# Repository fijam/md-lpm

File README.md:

# md-lpm

This project consists of hardware files and software for a coin-battery operated laser tester that fits in a MiniDisk case.

## Hardware

Schematics, BOM and PCB layout files are available in the hardware directory.

## Theory of operation

This is the nerdy bit, feel free to skip ahead.

The heart of this device is a silicon PIN photodiode (BPW34) operated in reverse-biased mode, which generates current proportional to light intensity. The MiniDisc standard uses 780nm near-infrared laser source for both playback (using the magneto-optic Kerr effect) and recording (for heating up the disc to its Curie temperature). The output power spans between 0.5 and 9mW, depending on the device. 

The selected photodiode has approx. 95% spectral sensitivity at 780nm. The reverse voltage of 3V from a manganese-dioxide lithium battery and load resistance of 1k Ohm allows for a linear response up to 5.5mW as given by: 
`Psat = (0.3 + VR)/RL * S` where VR is the reverse voltage [2.9 V], S is the photosensitivity at 780nm [0.58 A/W] and RL is the load resistance [1000 Ohm]. Photodiode series resistance is disregarded.

High correlation between the photodiode readout (10b referenced to Vdd) and the device refPw setting (in decimal) is achieved:

Shorter fragments of this polynomial (around 0.5-1mW for LrefPw/HrefPw and 4.5-5.5mW for WritPW) can be approximated with a linear regression. 

To discount the effect of battery voltage dropping as it discharges, internal voltage reference of 1.1V is used for LrefPw/HrefPw. For WritPw, the whole range of Vdd is used. The setting of WritPw does not require a high precision.

Each device comes with a calibration factor saved in `user_row` area of the EEPROM which is protected from accidental chip erase. This calibration factor (by default 100%) accounts for differences between components, photodiode alignment and assembly in the minidisc case. It is taken into account when calculating LrefPw and HrefPw.

The firmware of the microcontroller is configured with a BOD of ~2.6V which prevents the device from running on a discharged battery.

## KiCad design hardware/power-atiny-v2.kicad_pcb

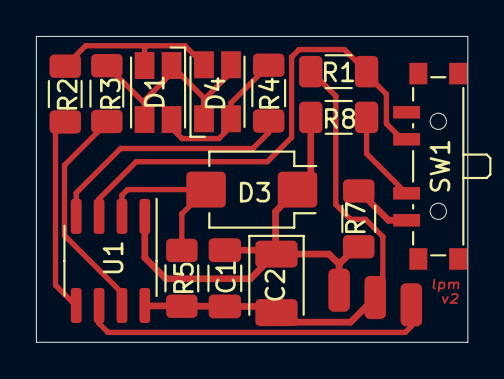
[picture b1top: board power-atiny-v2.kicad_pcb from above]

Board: 2 copper layers, 24.0 x 17.0 mm, 17 parts (0 on the bottom side), 13 nets.

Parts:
C1: 100nF; C_1206_3216Metric_Pad1.33x1.80mm_HandSolder
C2: 68uF; CP_EIA-3528-21_Kemet-B_Pad1.50x2.35mm_HandSolder
D1, D4: LED_Dual_ACAC; LED_Avago_PLCC4_3.2x2.8mm_CW_datasheet
D3: BPW34-SMD; Osram_SMD-DIL2_4.5x4.0mm
GND: SolderWirePad_1x01_SMD_1x2mm
R1: 249k; R_1206_3216Metric_Pad1.30x1.75mm_HandSolder
R2, R3, R4: 220; R_1206_3216Metric_Pad1.30x1.75mm_HandSolder
R5: 1k; R_1206_3216Metric_Pad1.30x1.75mm_HandSolder
R7: 480k; R_1206_3216Metric_Pad1.30x1.75mm_HandSolder
R8: 100k; R_1206_3216Metric_Pad1.30x1.75mm_HandSolder
SW1: SW_SP3T; SW_SP3T_PCM13
U1: ATtiny412-SS; SOIC-8_3.9x4.9mm_P1.27mm
UPDI: SolderWirePad_1x01_SMD_1x2mm
VCC: SolderWirePad_1x01_SMD_1x2mm

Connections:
GND: C1.2, C2.2, GND.1, R1.2, R5.2, U1.8
unnamed: D1.1, D1.4, D4.1, D4.4, R3.1
unnamed: D1.2, D4.3, R2.1
unnamed: D1.3, D4.2, R4.1
unnamed: D3.2, R5.1, U1.2
unnamed: R1.1, SW1.3, U1.3
unnamed: R2.2, U1.5
unnamed: R3.2, U1.7
unnamed: R4.2, U1.4
unnamed: R7.2, SW1.1
unnamed: R8.2, SW1.2
unnamed: U1.6, UPDI.1
VCC: C1.1, C2.1, D3.1, R7.1, R8.1, U1.1, VCC.1

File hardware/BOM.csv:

Id,Designator,Package,Quantity,Designation,Supplier and ref
1,R8,R_1206_3216Metric_Pad1.30x1.75mm_HandSolder,1,100k,
2,R1,R_1206_3216Metric_Pad1.30x1.75mm_HandSolder,1,249k,
3,C2,CP_EIA-3528-21_Kemet-B_Pad1.50x2.35mm_HandSolder,1,68uF,Optional, Kemet T case
4,SW1,SW_SP3T_PCM13,1,SW_SP3T,Nidec Copal CUS-13TB
5,D1,D4,LED_Avago_PLCC4_3.2x2.8mm_CW_datasheet,2,LED_Dual_ACAC,Avago HSMF-C155
6,U1,SOIC-8_3.9x4.9mm_P1.27mm,1,ATtiny412-SS,Microchip ATTINY212-SSNR
7,C1,C_1206_3216Metric_Pad1.33x1.80mm_HandSolder,1,100nF,
8,D3,Osram_SMD-DIL2_4.5x4.0mm,1,BPW34-SMD,Osram BPW34S
9,R2,R3,R4,R_1206_3216Metric_Pad1.30x1.75mm_HandSolder,3,220,
10,R5,R_1206_3216Metric_Pad1.30x1.75mm_HandSolder,1,1k,
11,R7,R_1206_3216Metric_Pad1.30x1.75mm_HandSolder,1,480k,

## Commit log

2022-02-04 Initial import
2022-02-04 Add lpm.py executable (via pyinstaller)
2022-02-04 Add BOM
2022-02-04 use tab separator for BOM
2022-04-10 Add 'suspend' mode, reformat comments
2022-11-20 Add the ability to clear the values from EEPROM
